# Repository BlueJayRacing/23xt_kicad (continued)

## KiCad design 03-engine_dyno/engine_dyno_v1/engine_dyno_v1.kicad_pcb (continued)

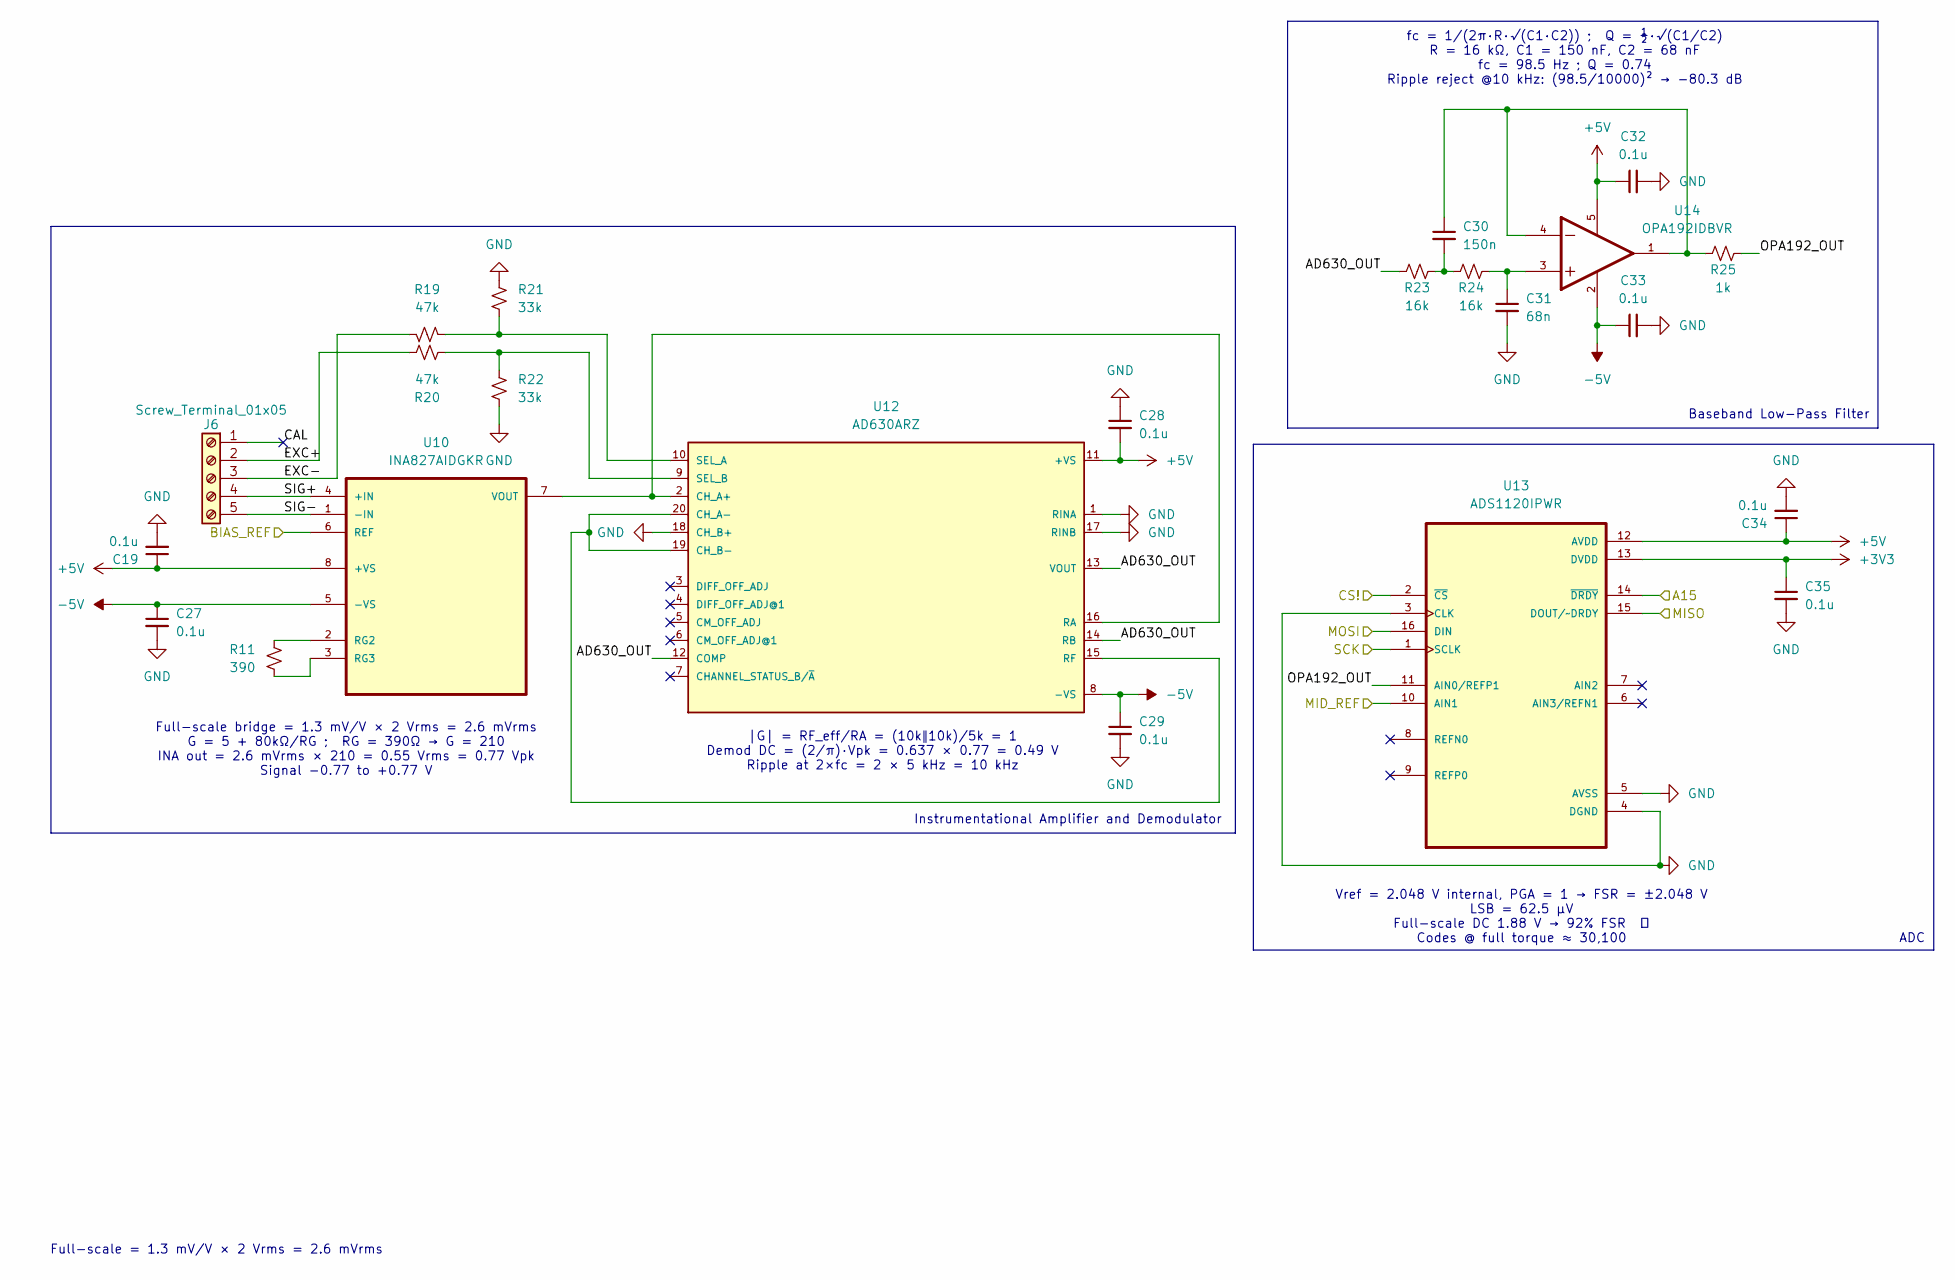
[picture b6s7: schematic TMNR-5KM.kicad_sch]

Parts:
C19, C27, C28, C29, C32, C33, C34, C35: 0.1u; C_0402_1005Metric
C30: 150n; C_0402_1005Metric
C31: 68n; C_0402_1005Metric
J6: Screw_Terminal_01x05; TerminalBlock_RND_205-00235_1x05_P5.08mm_Horizontal
R11: 390; R_0402_1005Metric
R19, R20: 47k; R_0402_1005Metric
R21, R22: 33k; R_0402_1005Metric
R23, R24: 16k; R_0402_1005Metric
R25: 1k; R_0402_1005Metric
U10: INA827AIDGKR; SOP65P490X110-8N; DigiKey_Part_Number 296-30588-1-ND
U12: AD630ARZ; SOIC127P1032X265-20N
U13: ADS1120IPWR; SOP65P640X120-16N
U14: OPA192IDBVR; SOT95P280X145-5N; PARTREV F

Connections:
+3V3: C35.1, U13.13 (DVDD); also elsewhere on the board
+5V: C19.1, C28.2, C32.1, C34.1, U10.8 (+VS), U12.11 (+VS), U13.12 (AVDD), U14.5; also elsewhere on the board
-5V: C27.1, C29.1, C33.1, U10.5 (-VS), U12.8 (-VS), U14.2; also elsewhere on the board
/MCU/A15: U13.14 (~DRDY); also elsewhere on the board
/MCU/CS_3: U13.2 (~CS); also elsewhere on the board
/MCU/MISO: U13.15 (DOUT/~DRDY); also elsewhere on the board
/MCU/MOSI: U13.16 (DIN); also elsewhere on the board
/MCU/SCK: U13.1 (SCLK); also elsewhere on the board
/Model1605/BIAS_REF: U10.6 (REF); also elsewhere on the board
/Model1605/MID_REF: U13.10 (AIN1); also elsewhere on the board
/TMNR-5KM/AD630_OUT: R23.1, U12.12 (COMP), U12.13 (VOUT), U12.14 (RB)
/TMNR-5KM/CAL: J6.1
/TMNR-5KM/EXC+: J6.2, R20.1
/TMNR-5KM/EXC-: J6.3, R19.1
/TMNR-5KM/OPA192_OUT: R25.2, U13.11 (AIN0/REFP1)
/TMNR-5KM/SIG+: J6.4, U10.4 (+IN)
/TMNR-5KM/SIG-: J6.5, U10.1 (-IN)
GND: C19.2, C27.2, C28.1, C29.2, C31.2, C32.2, C33.2, C34.2, C35.2, R21.2, R22.1, U12.1 (RINA), U12.17 (RINB), U12.18 (CH_B+), U13.3 (CLK), U13.4 (DGND), U13.5 (AVSS); also elsewhere on the board
unnamed: C30.1, R25.1, U14.1, U14.4
unnamed: C30.2, R23.2, R24.1
unnamed: C31.1, R24.2, U14.3
unnamed: R11.1, U10.2 (RG2)
unnamed: R11.2, U10.3 (RG3)
unnamed: U10.7 (VOUT), U12.2 (CH_A+), U12.16 (RA)
unnamed: U12.15 (RF), U12.19 (CH_B-), U12.20 (CH_A-)
unnamed: R19.2, R21.1, U12.10 (SEL_A)
unnamed: R20.2, R22.2, U12.9 (SEL_B)

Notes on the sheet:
Baseband Low-Pass Filter
fc = 1/(2π·R·√(C1·C2)) ; Q = ½·√(C1/C2) R = 16 kΩ, C1 = 150 nF, C2 = 68 nF fc = 98.5 Hz ; Q = 0.74 Ripple reject @10 kHz: (98.5/10000)² → −80.3 dB
Full-scale bridge = 1.3 mV/V × 2 Vrms = 2.6 mVrms G = 5 + 80kΩ/RG ; RG = 390Ω → G = 210 INA out = 2.6 mVrms × 210 = 0.55 Vrms = 0.77 Vpk Signal −0.77 to +0.77 V
Full-scale = 1.3 mV/V × 2 Vrms = 2.6 mVrms
Vref = 2.048 V internal, PGA = 1 → FSR = ±2.048 V LSB = 62.5 µV Full-scale DC 1.88 V → 92% FSR ✓ Codes @ full torque ≈ 30,100
|G| = RF_eff/RA = (10k‖10k)/5k = 1 Demod DC = (2/π)·Vpk = 0.637 × 0.77 = 0.49 V Ripple at 2×fc = 2 × 5 kHz = 10 kHz
Instrumentational Amplifier and Demodulator
ADC

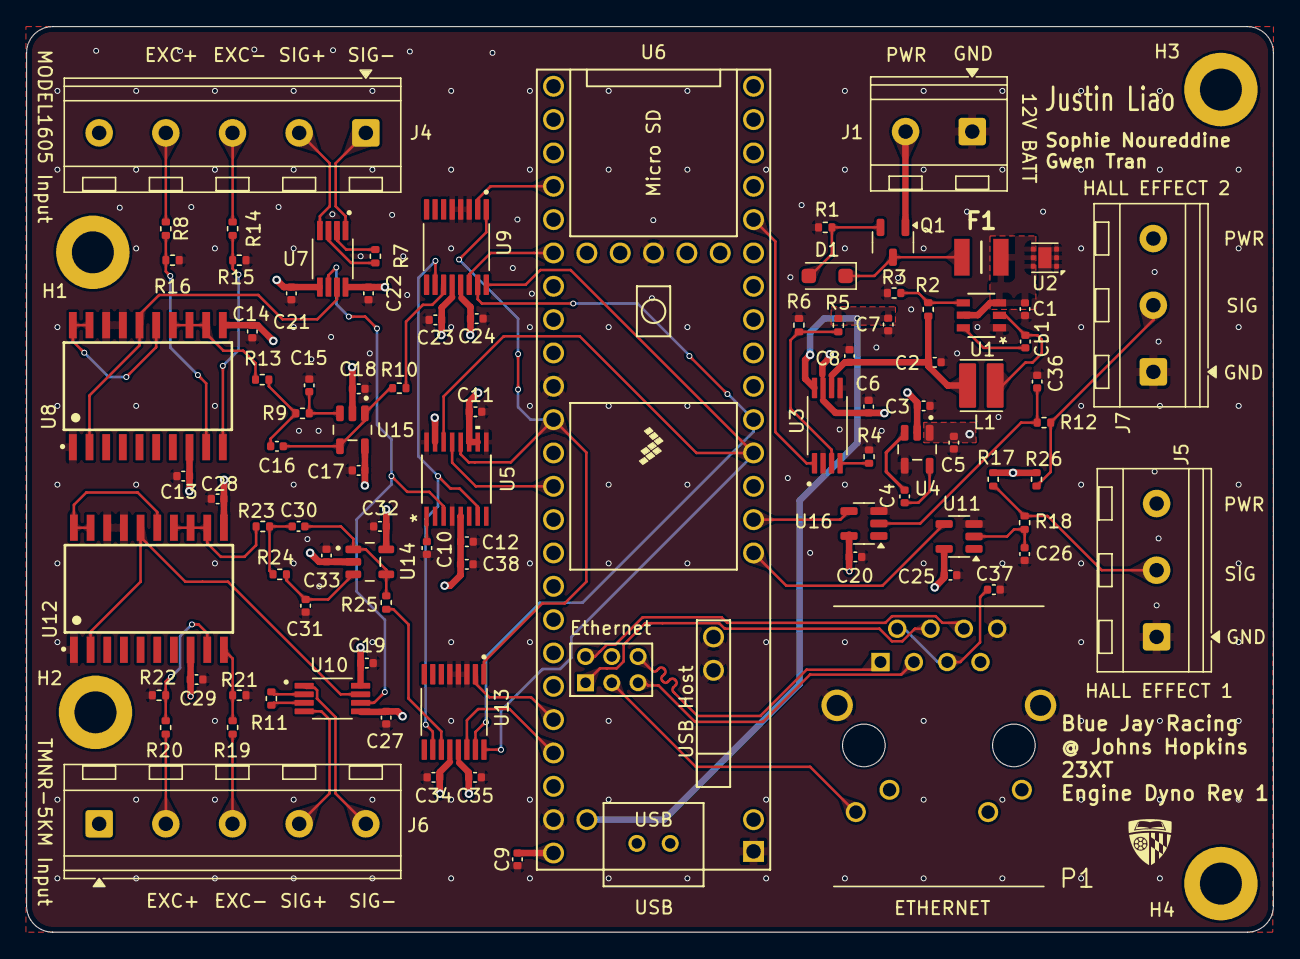
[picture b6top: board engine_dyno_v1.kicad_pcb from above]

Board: 4 copper layers, 95.0 x 69.0 mm, 95 parts (0 on the bottom side), 71 nets.

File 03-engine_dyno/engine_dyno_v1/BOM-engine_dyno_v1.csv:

Item # ,Designator,DNP,Qty,Manufacturer,LCSC,Mfg Part #,Description/Value,Package/Footprint,Type
1,"C1,C6,C38",,3,,,,"Ceramic capacitor, 10uF, 0402",0402 (1005 Metric),SMD
2,C2,,1,,,,"Ceramic capacitor, 47uF, 0402",0402 (1005 Metric),SMD
3,"C3,C4,C5",,3,,,,"Ceramic capacitor, 1uF, 0402",0402 (1005 Metric),SMD
4,"C7,C8,Cb1,C9,C10,C11,C12,C13,C14,C17,C18,C19,C20,C21,C22,C23,C24,C25,C27,C28,C29,C32,C33,C34,C35,C37",,26,,,,"Ceramic capacitor, 100nF, 0402",0402 (1005 Metric),SMD
5,"C15,C31",,2,,,,"Ceramic capacitor, 68nF, 0402",0402 (1005 Metric),SMD
6,"C16,C30",,2,,,,"Ceramic capacitor, 150nF, 0402",0402 (1005 Metric),SMD
7,"C26,C36",,2,,,,"Ceramic capacitor, 1nF, 0402",0402 (1005 Metric),SMD
8,"R1,R2,R5,R6,R8,R14",,6,,,,"Chip resistor, 100kΩ, 0402",0402 (1005 Metric),SMD
9,R3,,1,,,,"Chip resistor, 13.7kΩ, 0402",0402 (1005 Metric),SMD
10,R4,,1,,,,"Chip resistor, 500Ω, 0402",0402 (1005 Metric),SMD
11,R7,,1,,,,"Chip resistor, 1.5kΩ, 0402",0402 (1005 Metric),SMD
12,"R9,R13,R23,R24",,4,,,,"Chip resistor, 16kΩ, 0402",0402 (1005 Metric),SMD
13,"R10,R25",,2,,,,"Chip resistor, 1kΩ, 0402",0402 (1005 Metric),SMD
14,R11,,1,,,,"Chip resistor, 390Ω, 0402",0402 (1005 Metric),SMD
15,"R12,R17,R18,R26",,4,,,,"Chip resistor, 4.7kΩ, 0402",0402 (1005 Metric),SMD
16,"R15,R16",,2,,,,"Chip resistor, 20kΩ, 0402",0402 (1005 Metric),SMD
17,"R19,R20",,2,,,,"Chip resistor, 47kΩ, 0402",0402 (1005 Metric),SMD
18,"R21,R22",,2,,,,"Chip resistor, 33kΩ, 0402",0402 (1005 Metric),SMD
19,L1,,1,Würth Elektronik,,74438336100,3.0 × 3.0 × 2.0 mm power inductor; IRP 1.65A; Isat 1.55A at 10% / 3.0A at 30%.,WE-MAPI 3020,SMD

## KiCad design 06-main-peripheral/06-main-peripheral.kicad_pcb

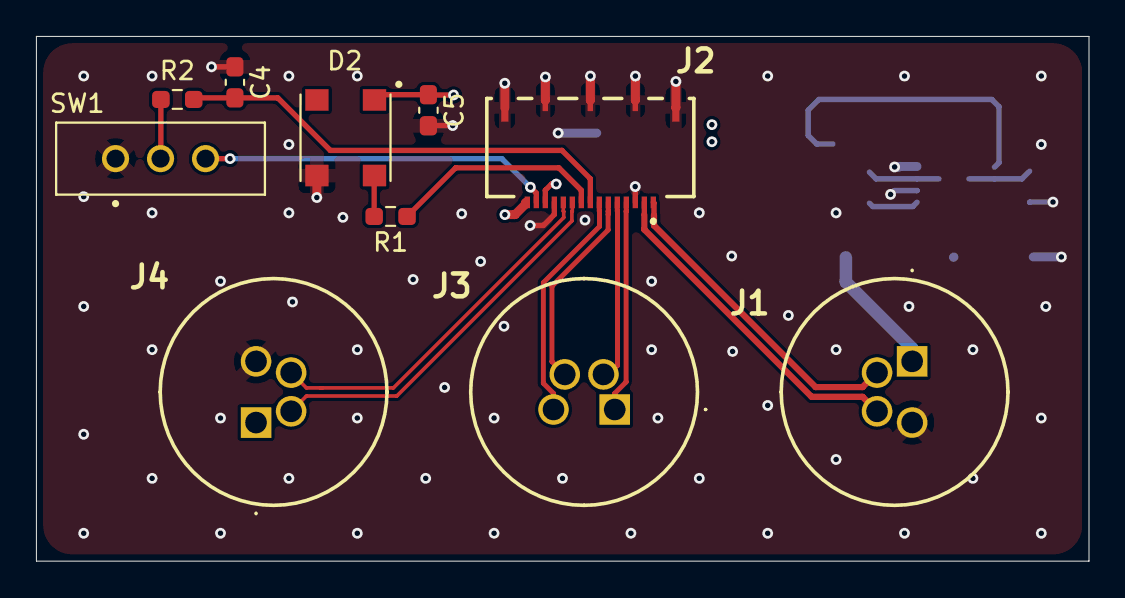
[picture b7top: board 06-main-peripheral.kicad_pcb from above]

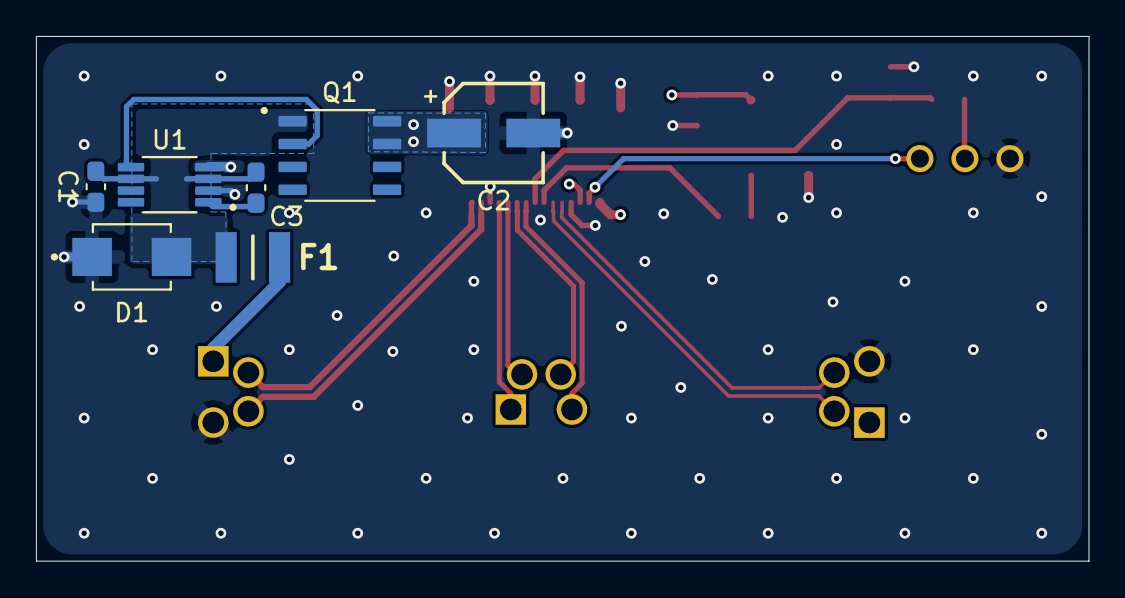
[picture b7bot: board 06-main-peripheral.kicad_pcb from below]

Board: 4 copper layers, 58.5 x 29.2 mm, 17 parts (7 on the bottom side), 20 nets.

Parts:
C1: 22nF; C_0603_1608Metric_Pad1.08x0.95mm_HandSolder
C2: 47uF; WCAP-ASLI_5X5.5_DXL_
C3: 0.1uF; C_0603_1608Metric_Pad1.08x0.95mm_HandSolder
C4, C5: 100nF; C_0603_1608Metric_Pad1.08x0.95mm_HandSolder
D1: SMBJ6.0CA; DIOM4336X265N
D2: LED 5050
F1: 0ZCH0050FF2G
J1, J3, J4: T4040014041000
J2: FH-41-15S-0.5SH-05_; FH4115S05SH05
Q1: DMN3018SSD-13; SOIC127P600X170-8N
R1: 500; R_0603_1608Metric_Pad0.98x0.95mm_HandSolder
R2: 10k; R_0603_1608Metric_Pad0.98x0.95mm_HandSolder
SW1: 100SP1K1B25M1QEH-ND; SW_EG1218
U1: LM74700-Q1; LM74610QDGKRQ1

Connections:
3.3V: J2.14, SW1.3 (A)
5V: C5.1, D2.3 (VDD), J2.15, J4.1
CAN_N: J2.11, J4.4
CAN_P: J2.10, J4.2
GND: C1.2, C2.2, C4.1, C5.2, D1.1 (A1), D2.1 (GND), J1.3, J2.3, J2.12, J2.G1, J2.G2, J2.G3, J2.MP2, J4.3, SW1.1 (C), U1.2 (GND), U1.4 (CATHODE)
LED_CONTROL: J2.9, R1.1
unnamed: C1.1, C3.1, D1.2 (A2), F1.1, Q1.1 (S), U1.3 (EN), U1.6 (ANODE)
unnamed: D2.2 (DIN), R1.2
unnamed: F1.2, J1.1
unnamed: Q1.2 (G), U1.5 (GATE)
unnamed: R2.2, SW1.2 (B)
unnamed: C3.2, U1.1 (VCAP)
RX_N: J2.5, J3.2
RX_P: J2.4, J3.1
TX_N: J2.6, J3.4
TX_P: J2.7, J3.3
USB_5V: C2.1, J2.13, Q1.7 (D), Q1.8
USB_D_N: J1.2, J2.1
USB_D_P: J1.4, J2.2
USB_SEL: C4.2, J2.8, R2.1

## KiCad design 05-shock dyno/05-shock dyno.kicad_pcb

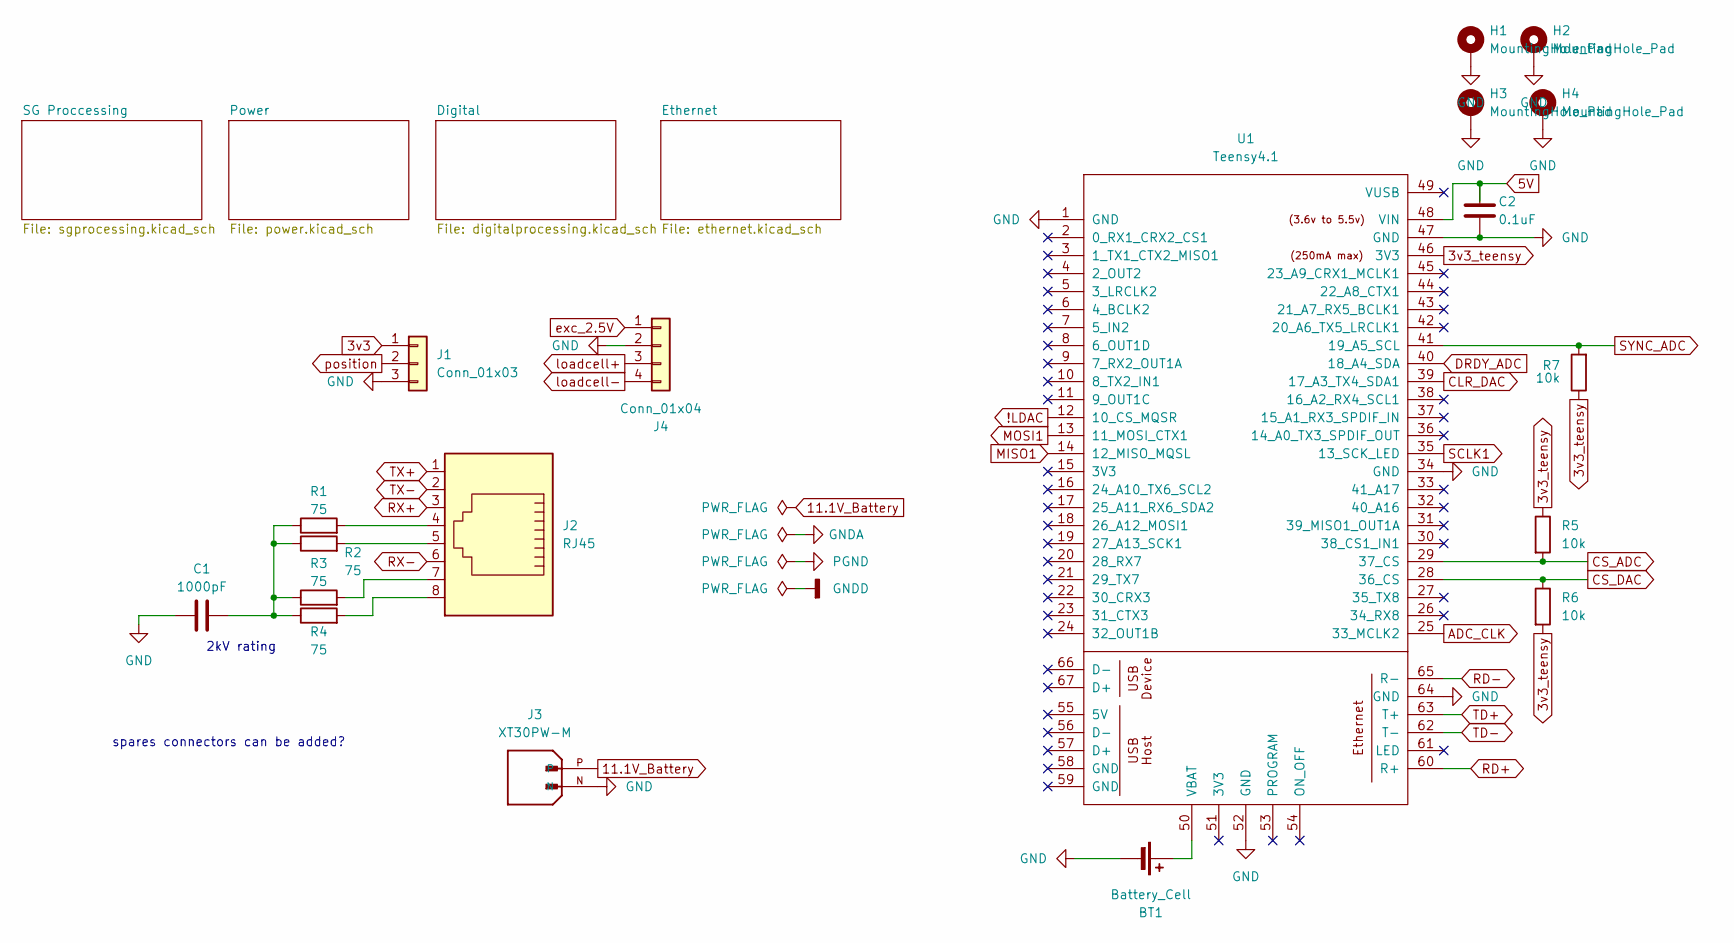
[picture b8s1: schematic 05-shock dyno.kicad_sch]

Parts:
BT1: Battery_Cell; BatteryHolder_LINX_BAT-HLD-012-SMT
C1: 1000pF; C_1206_3216Metric
C2: 0.1uF; C_0402_1005Metric
H1, H2, H3, H4: MountingHole_Pad; MountingHole_4.3mm_M4_DIN965_Pad
J1: Conn_01x03; JST_XH_B3B-XH-A_1x03_P2.50mm_Vertical
J2: RJ45; TE_RJ45-8N-B
J3: XT30PW-M; AMASS_XT30PW-M; PARTREV 1.2
J4: Conn_01x04; JST_XH_B4B-XH-A_1x04_P2.50mm_Vertical
R1, R2, R3, R4: 75; C_0402_1005Metric
R5, R6, R7: 10k; C_0402_1005Metric
U1: Teensy4.1; Teensy41

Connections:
3v3: J1.1; also elsewhere on the board
3v3_teensy: R5.1, R6.2, R7.1, U1.46 (3V3); also elsewhere on the board
5V: C2.1, U1.48 (VIN); also elsewhere on the board
11.1V_Battery: J3.P; also elsewhere on the board
!LDAC: U1.12 (10_CS_MQSR); also elsewhere on the board
ADC_CLK: U1.25 (33_MCLK2); also elsewhere on the board
CLR_DAC: U1.39 (17_A3_TX4_SDA1); also elsewhere on the board
CS_ADC: R5.2, U1.29 (37_CS); also elsewhere on the board
CS_DAC: R6.1, U1.28 (36_CS); also elsewhere on the board
DRDY_ADC: U1.40 (18_A4_SDA); also elsewhere on the board
GND: BT1.2 (-), C1.1, C2.2, H1.1, H2.1, H3.1, H4.1, J1.3, J3.N, J4.2, U1.1 (GND), U1.34 (GND), U1.47 (GND), U1.52 (GND), U1.64 (GND); also elsewhere on the board
MISO1: U1.14 (12_MISO_MQSL); also elsewhere on the board
MOSI1: U1.13 (11_MOSI_CTX1); also elsewhere on the board
unnamed: BT1.1 (+), U1.50 (VBAT)
unnamed: C1.2, R1.1, R2.1, R3.1, R4.1
unnamed: J2.4, R1.2
unnamed: J2.5, R2.2
unnamed: J2.7, R3.2
unnamed: J2.8, R4.2
RD+: U1.60 (R+); also elsewhere on the board
RD-: U1.65 (R-); also elsewhere on the board
RX+: J2.3; also elsewhere on the board
RX-: J2.6; also elsewhere on the board
SCLK1: U1.35 (13_SCK_LED); also elsewhere on the board
SYNC_ADC: R7.2, U1.41 (19_A5_SCL); also elsewhere on the board
TD+: U1.63 (T+); also elsewhere on the board
TD-: U1.62 (T-); also elsewhere on the board
TX+: J2.1; also elsewhere on the board
TX-: J2.2; also elsewhere on the board
exc_2.5V: J4.1; also elsewhere on the board
loadcell+: J4.3; also elsewhere on the board
loadcell-: J4.4; also elsewhere on the board
position: J1.2; also elsewhere on the board

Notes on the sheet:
2kV rating
spares connectors can be added?

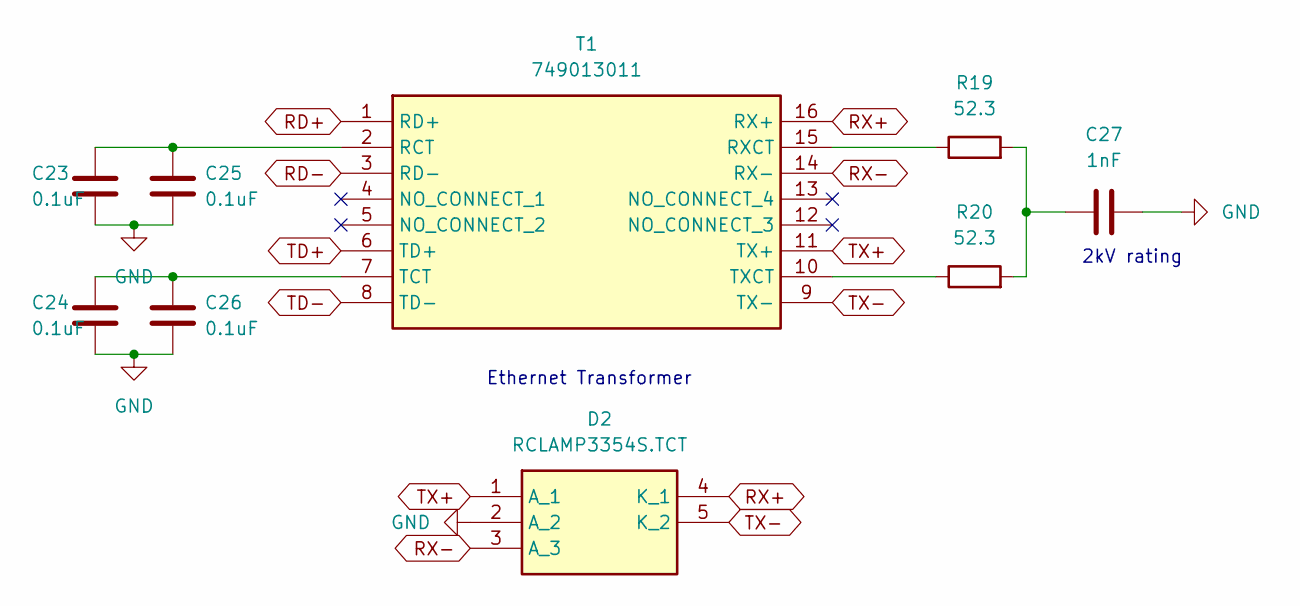
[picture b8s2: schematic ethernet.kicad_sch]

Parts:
C23, C24, C25, C26: 0.1uF; C_0402_1005Metric
C27: 1nF; C_1206_3216Metric
D2: RCLAMP3354S.TCT; SOT-23-5; Mouser Part Number 947-RCLAMP3354S.TCT
R19, R20: 52.3; C_0402_1005Metric
T1: 749013011; Mouser Part Number 710-749013011

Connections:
GND: C23.2, C24.2, C25.2, C26.2, C27.1, D2.2 (A_2); also elsewhere on the board
unnamed: C27.2, R19.2, R20.2
unnamed: C23.1, C25.1, T1.2 (RCT)
unnamed: R19.1, T1.15 (RXCT)
unnamed: C24.1, C26.1, T1.7 (TCT)
unnamed: R20.1, T1.10 (TXCT)
RD+: T1.1 (RD+); also elsewhere on the board
RD-: T1.3 (RD-); also elsewhere on the board
RX+: D2.4 (K_1), T1.16 (RX+); also elsewhere on the board
RX-: D2.3 (A_3), T1.14 (RX-); also elsewhere on the board
TD+: T1.6 (TD+); also elsewhere on the board
TD-: T1.8 (TD-); also elsewhere on the board
TX+: D2.1 (A_1), T1.11 (TX+); also elsewhere on the board
TX-: D2.5 (K_2), T1.9 (TX-); also elsewhere on the board

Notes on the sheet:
2kV rating
Ethernet Transformer

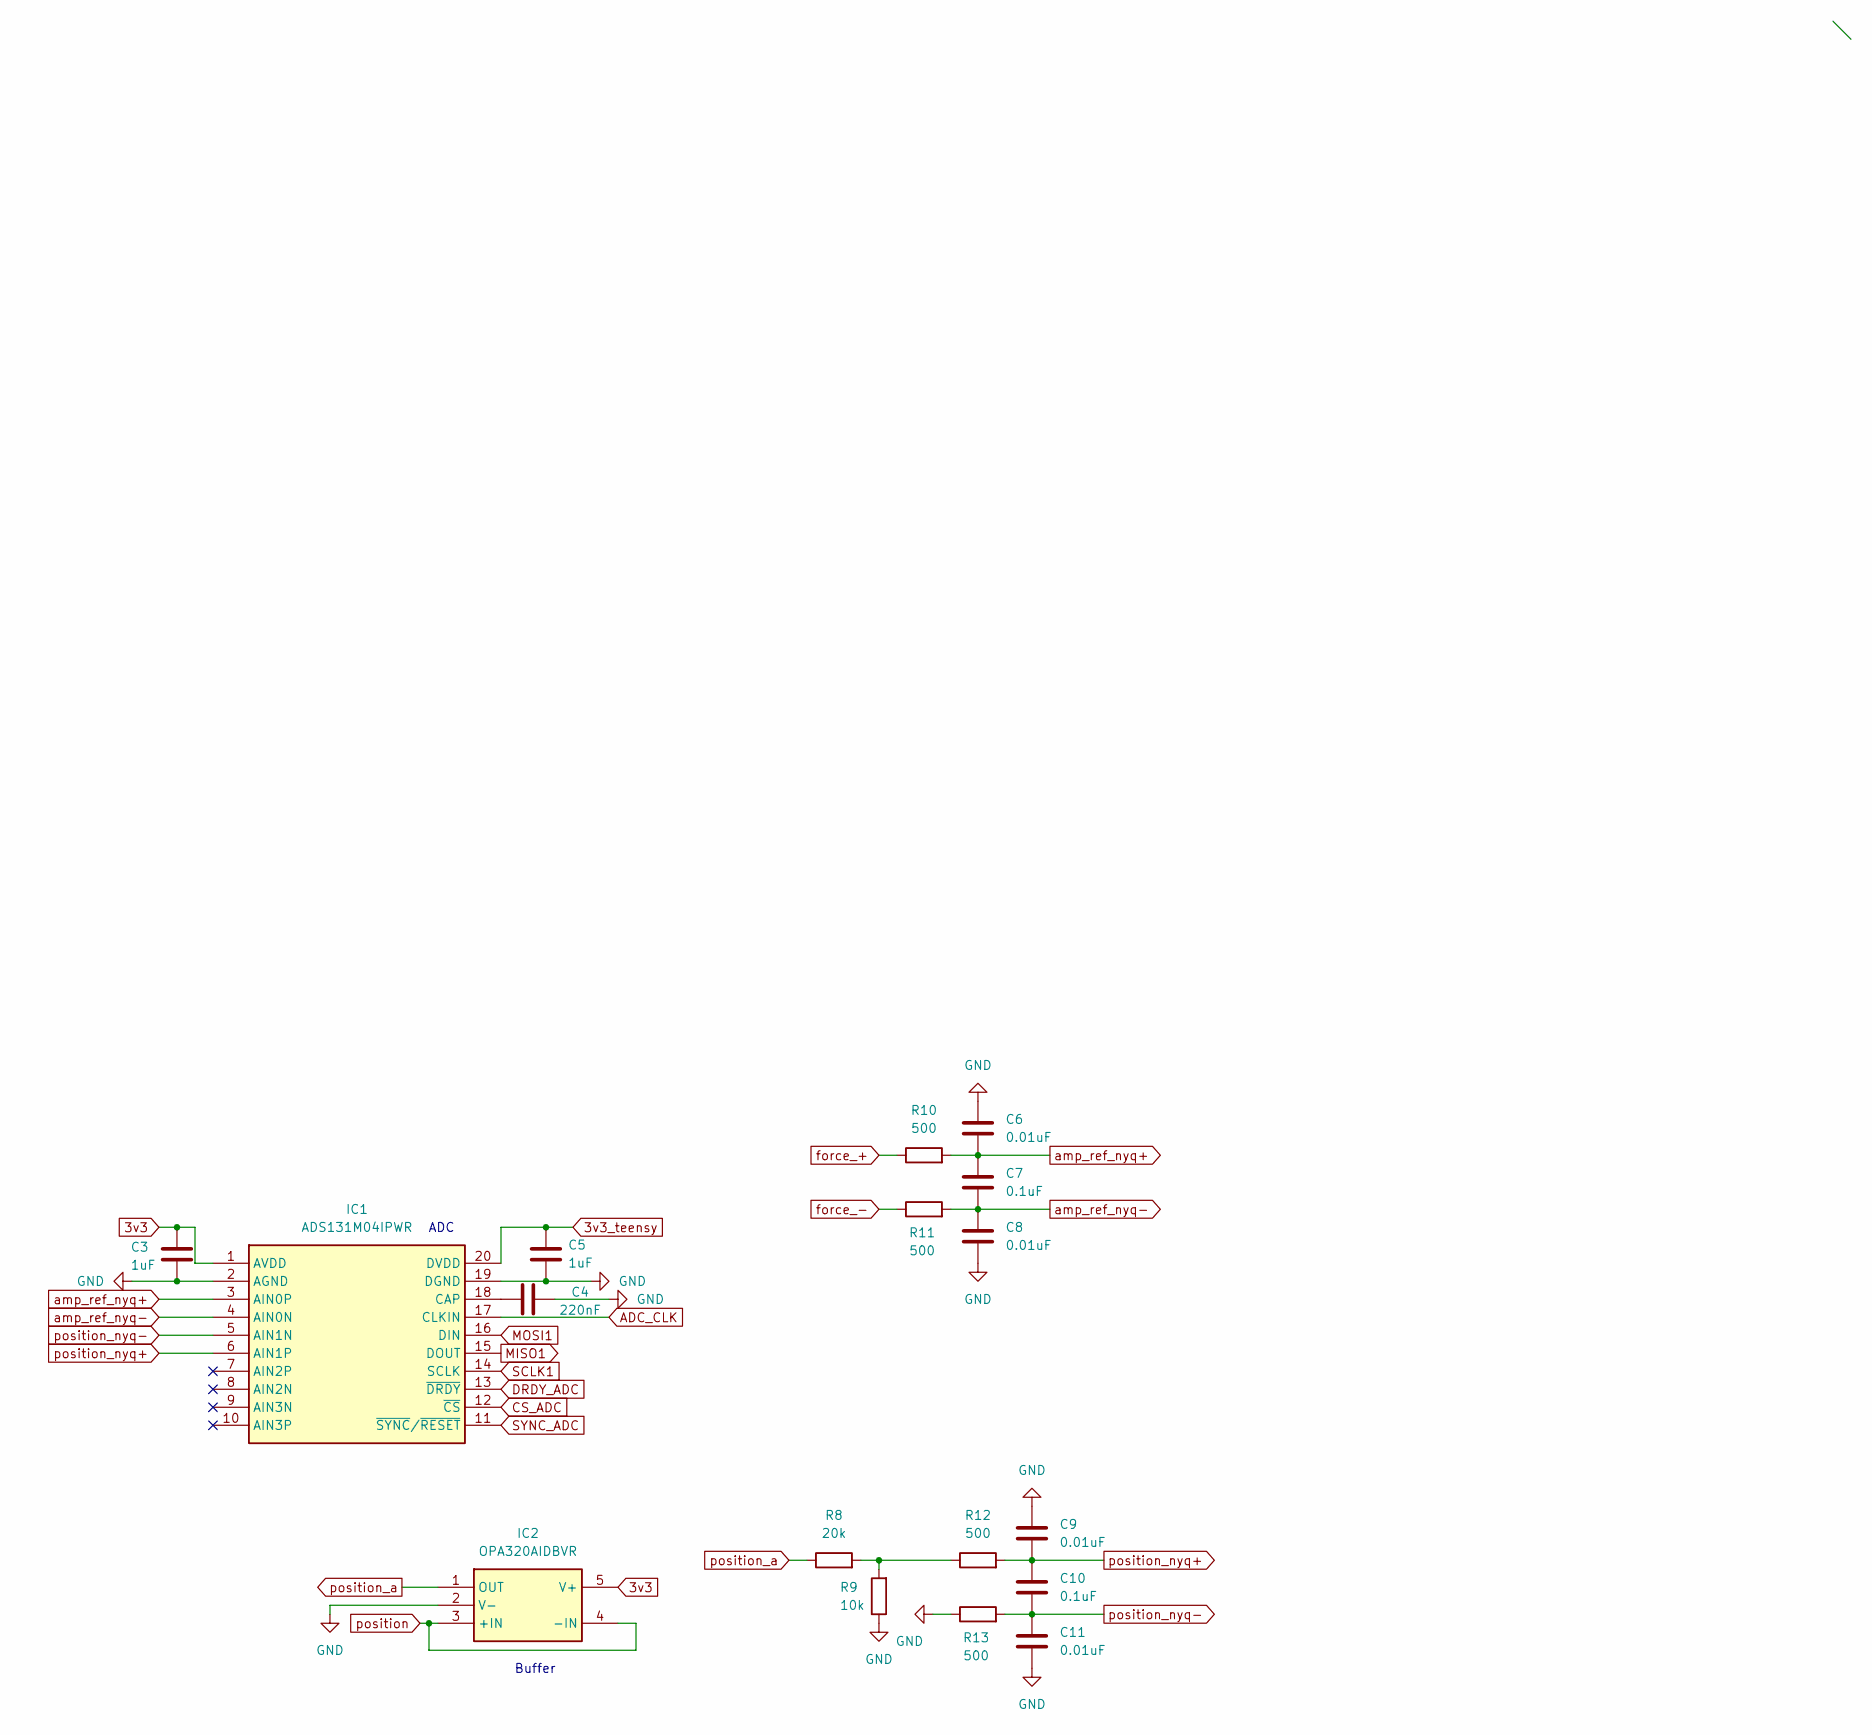
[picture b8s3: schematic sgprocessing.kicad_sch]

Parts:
C3, C5: 1uF; C_0603_1608Metric
C4: 220nF; C_0603_1608Metric
C6, C8, C9, C11: 0.01uF; C_0603_1608Metric
C7, C10: 0.1uF; C_1206_3216Metric
IC1: ADS131M04IPWR; SOP65P640X120-20N; Mouser Part Number 595-ADS131M04IPWR
IC2: OPA320AIDBVR; SOT95P280X145-5N; Mouser Part Number 595-OPA320AIDBVR
R8: 20k; C_0603_1608Metric
R9: 10k; C_0603_1608Metric
R10, R11, R12, R13: 500; C_0603_1608Metric

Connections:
3v3: C3.1, IC1.1 (AVDD), IC2.5 (V+); also elsewhere on the board
3v3_teensy: C5.1, IC1.20 (DVDD); also elsewhere on the board
ADC_CLK: IC1.17 (CLKIN); also elsewhere on the board
CS_ADC: IC1.12 (~CS); also elsewhere on the board
DRDY_ADC: IC1.13 (~DRDY); also elsewhere on the board
GND: C3.2, C4.1, C5.2, C6.1, C8.2, C9.1, C11.2, IC1.2 (AGND), IC1.19 (DGND), IC2.2 (V-), R9.1, R13.1; also elsewhere on the board
MISO1: IC1.15 (DOUT); also elsewhere on the board
MOSI1: IC1.16 (DIN); also elsewhere on the board
unnamed: C4.2, IC1.18 (CAP)
unnamed: R8.2, R9.2, R12.1
SCLK1: IC1.14 (SCLK); also elsewhere on the board
SYNC_ADC: IC1.11 (~SYNC/~RESET); also elsewhere on the board
amp_ref_nyq+: C6.2, C7.1, IC1.3 (AIN0P), R10.2
amp_ref_nyq-: C7.2, C8.1, IC1.4 (AIN0N), R11.2
force_+: R10.1; also elsewhere on the board
force_-: R11.1; also elsewhere on the board
position: IC2.3 (+IN), IC2.4 (-IN); also elsewhere on the board
position_a: IC2.1 (OUT), R8.1
position_nyq+: C9.2, C10.1, IC1.6 (AIN1P), R12.2
position_nyq-: C10.2, C11.1, IC1.5 (AIN1N), R13.2

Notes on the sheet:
Buffer
ADC

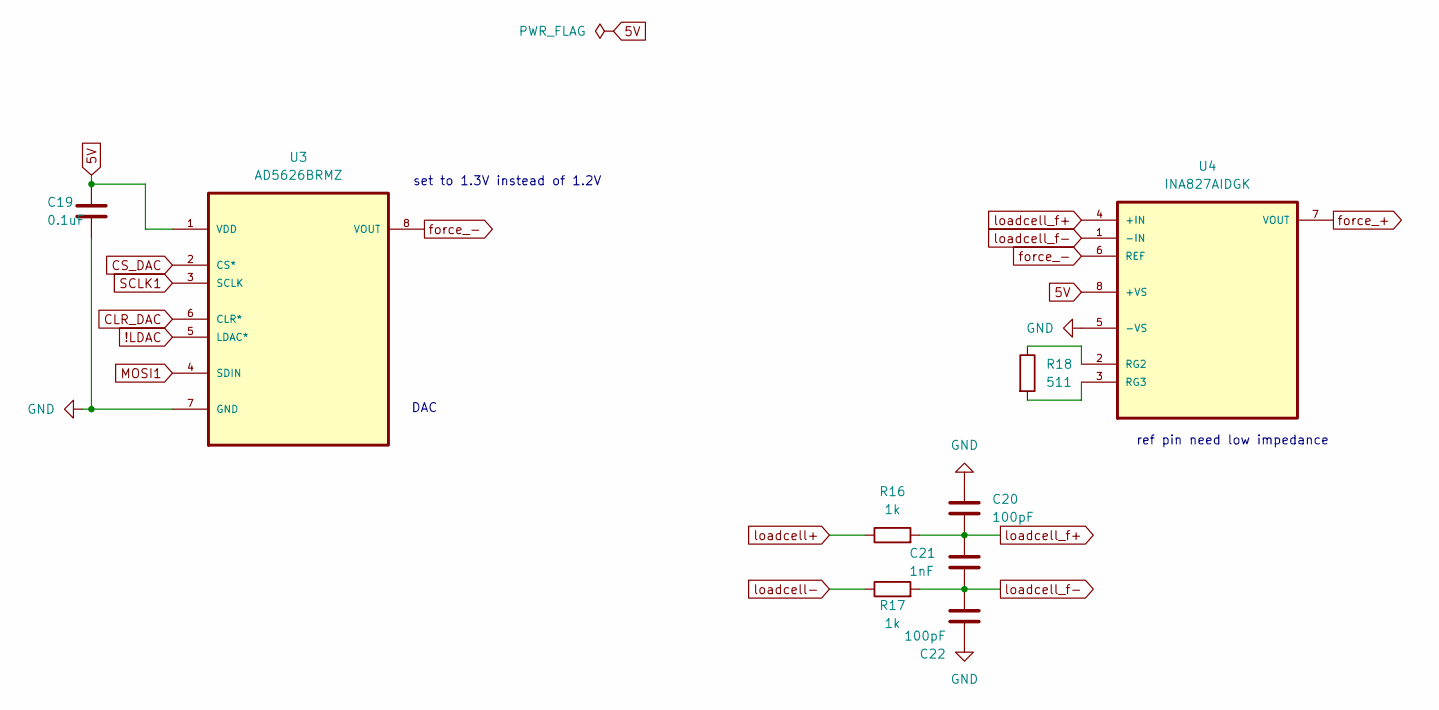
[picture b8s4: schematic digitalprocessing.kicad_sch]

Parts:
C19: 0.1uF; C_0402_1005Metric
C20, C22: 100pF; C_0603_1608Metric
C21: 1nF; C_0603_1608Metric
R16, R17: 1k; C_0603_1608Metric
R18: 511; C_0805_2012Metric
U3: AD5626BRMZ; MPN AD5626BRMZ
U4: INA827AIDGK

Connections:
5V: C19.1, U3.1 (VDD), U4.8 (+VS); also elsewhere on the board
!LDAC: U3.5 (LDAC*); also elsewhere on the board
CLR_DAC: U3.6 (CLR*); also elsewhere on the board
CS_DAC: U3.2 (CS*); also elsewhere on the board
GND: C19.2, C20.1, C22.1, U3.7 (GND), U4.5 (-VS); also elsewhere on the board
MOSI1: U3.4 (SDIN); also elsewhere on the board
unnamed: R18.1, U4.2 (RG2)
unnamed: R18.2, U4.3 (RG3)
SCLK1: U3.3 (SCLK); also elsewhere on the board
force_+: U4.7 (VOUT); also elsewhere on the board
force_-: U3.8 (VOUT), U4.6 (REF); also elsewhere on the board
loadcell+: R16.1; also elsewhere on the board
loadcell-: R17.1; also elsewhere on the board
loadcell_f+: C20.2, C21.1, R16.2, U4.4 (+IN)
loadcell_f-: C21.2, C22.2, R17.2, U4.1 (-IN)

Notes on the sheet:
DAC
set to 1.3V instead of 1.2V
ref pin need low impedance

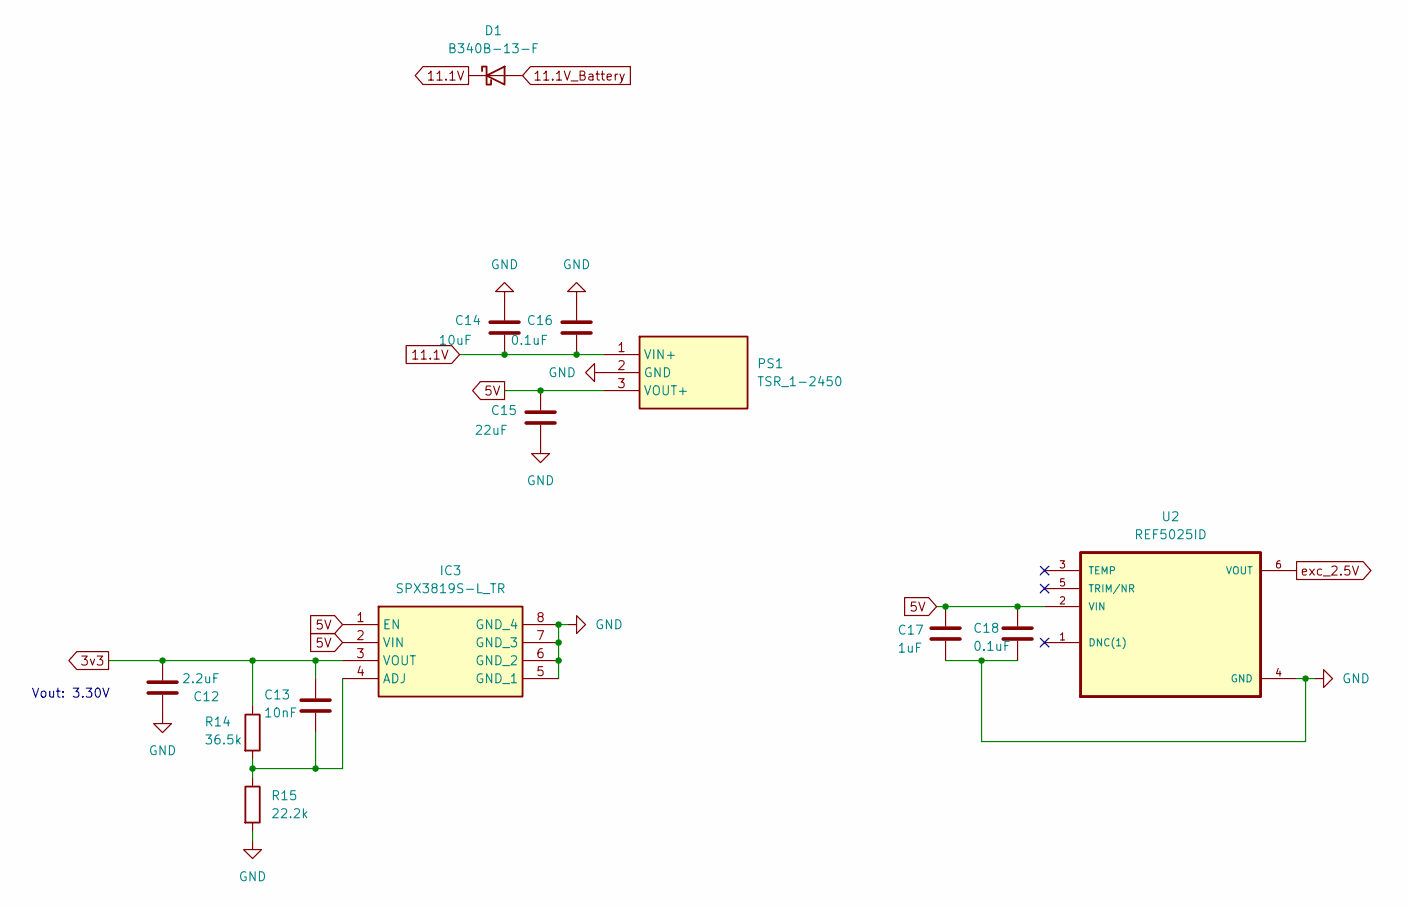
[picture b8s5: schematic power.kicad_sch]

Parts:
C12: 2.2uF; C_0805_2012Metric
C13: 10nF; C_0603_1608Metric
C14: 10uF; C_1206_3216Metric
C15: 22uF; C_1210_3225Metric
C16: 0.1uF; C_1206_3216Metric
C17: 1uF; C_0805_2012Metric
C18: 0.1uF; C_0603_1608Metric
D1: B340B-13-F; DIOM5336X250N
IC3: SPX3819S-L_TR; SOIC127P600X175-8N; Mouser Part Number 701-SPX3819S-L/TR
PS1: TSR_1-2450; TSR-1-24120; Mouser Part Number 495-TSR-1-2450
R14: 36.5k; C_0603_1608Metric
R15: 22.2k; C_0603_1608Metric
U2: REF5025ID; REF5025

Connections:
3v3: C12.1, C13.2, IC3.3 (VOUT), R14.1; also elsewhere on the board
5V: C15.1, C17.1, C18.1, IC3.1 (EN), IC3.2 (VIN), PS1.3 (VOUT+), U2.2 (VIN); also elsewhere on the board
11.1V: C14.2, C16.2, D1.1 (K), PS1.1 (VIN+)
11.1V_Battery: D1.2 (A); also elsewhere on the board
GND: C12.2, C14.1, C15.2, C16.1, C17.2, C18.2, IC3.5 (GND_1), IC3.6 (GND_2), IC3.7 (GND_3), IC3.8 (GND_4), PS1.2 (GND), R15.2, U2.4 (GND); also elsewhere on the board
unnamed: C13.1, IC3.4 (ADJ), R14.2, R15.1
exc_2.5V: U2.6 (VOUT); also elsewhere on the board

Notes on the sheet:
Vout: 3.30V

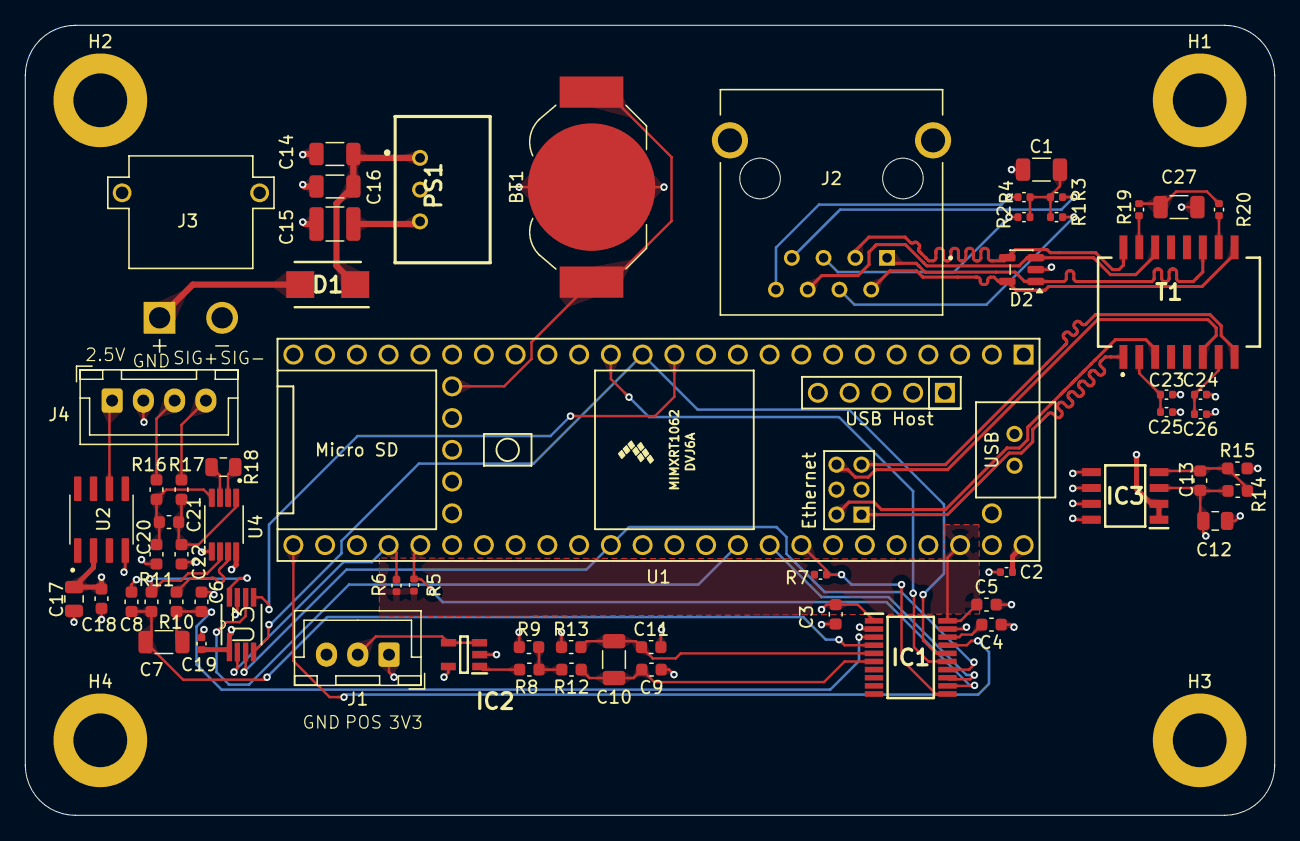
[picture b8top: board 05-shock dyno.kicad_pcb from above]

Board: 4 copper layers, 100.0 x 63.2 mm, 67 parts (0 on the bottom side), 53 nets.

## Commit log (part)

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2026-06-15 created project
2026-06-22 first try at kicad
2026-06-22 initial stm32 and ldo schematic
2026-06-22 add gitignore to exclude ds_store
2026-06-22 add magnetometer and can transceiver schematic
2026-06-25 schematic work
2026-06-25 add usbc flash and boot/reset
2026-06-30 transducer and hall preliminary design
